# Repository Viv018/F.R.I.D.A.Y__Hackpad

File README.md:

# F.R.I.D.A.Y__Hackpad
This is a Macro pad with a 3x3 key pad along with a rotary encoder and a 0.91 QLED screen for my HACKCLUB project
# F.R.I.D.A.Y

A custom 3×3 macropad with a rotary encoder, 0.91" OLED, and per-key SK6812 RGB lighting, built around the Seeeduino XIAO.

I named it F.R.I.D.A.Y because I wanted something that feels like a helpful little assistant sitting on my desk and cause i am a big marvel fan.

### Features
- 9 mechanical switches (3×3 matrix)
- Rotary encoder with push button
- 0.91" 128×32 OLED display
- 8× SK6812MINI-E reverse-mount RGB LEDs
- Seeed XIAO RP2040
- Fully open source

### Photos

**Schematic**

**PCB**
" src="https://github.com/user-attachments/assets/fc30a773-a280-402c-9867-2068fab1f9ea" />
)

**Case**
 - Autodesk Fusion (Trial ends in 24 days)  8_13_2026 5_06_41 PM.png)

### Bill of Materials

| Part                        | Quantity | Notes                          |
|----------------------------|----------|--------------------------------|
| Seeeduino XIAO             | 1        | RP2040 version                 |
| MX-style switches          | 9        | Any MX compatible              |
| SK6812MINI-E               | 8        | Reverse mount                  |
| 1N4148 diodes              | 9        |                                |
| Rotary Encoder (EC11)      | 1        | With push switch               |
| 0.91" OLED                 | 1        | I2C, 128×32                    |
| Keycaps                    | 9        | 1u                             |
| M3 screws + heat-set inserts | 4      | For the case                   |

### Firmware
This project uses **QMK**

The firmware is located in the `/Firmware` folder.

### Case
The case is a simple two-part sandwich design made in Fusion 360.  
STL/STEP files are available in the `/CAD` and `/production` folders.

### Credits
Designed for Hack Club’s Hackpad program by BATMANNN BABYYY

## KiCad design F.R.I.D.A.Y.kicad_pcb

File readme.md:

# F.R.I.D.A.Y.

This is my custom macropad, F.R.I.D.A.Y. I designed the schematic and PCB
myself in KiCad and wrote the firmware on top of QMK. It's a 3x3 key
matrix (9 keys total, one of them being the rotary encoder's own push
switch), plus the encoder for rotation input, a small OLED screen, and
RGB lighting.

## What's on it

- Seeed XIAO RP2040 as the brains
- 3x3 switch matrix (9 keys), with SW10 (the encoder's push button)
  built into the matrix as one of the 9
- A rotary encoder for scrolling / volume / media control
- A 0.91" OLED (128x32) that shows which layer is active
- 8x SK6812 addressable RGB LEDs

## Pin mapping

I worked this out straight from my schematic:

| Net                | XIAO pin | RP2040 GPIO |
|---------------------|----------|-------------|
| Row 0               | D0       | GP26        |
| Row 1               | D1       | GP27        |
| Row 2               | D2       | GP28        |
| Col 0               | D3       | GP29        |
| SDA (OLED)          | D4       | GP6         |
| SCL (OLED)          | D5       | GP7         |
| PIN7 -> DIN (LEDs)  | D6       | GP0         |
| Col 1               | D7       | GP1         |
| Col 2               | D8       | GP2         |
| ENC_A               | D9       | GP4         |
| ENC_B               | D10      | GP3         |

Key layout, matching the silkscreen on my PCB:

```
[SW10] [SW8] [SW9]     <- SW10 is the encoder's own push button
[SW1]  [SW2] [SW3]
[SW4]  [SW5] [SW6]
```

## Firmware

Built on QMK. There are two layers - a base layer for my everyday keys
and media, and an Fn layer (hold the bottom-right key) for extra
shortcuts. The encoder does volume on the base layer and skips tracks
on the Fn layer. The OLED just shows the current layer for now.

### Building it

```bash
python3 -m pip install qmk
qmk setup
```

Then drop this whole `friday` folder into `~/qmk_firmware/keyboards/friday/`
so it looks like:

```
qmk_firmware/keyboards/friday/
├── keyboard.json
├── config.h
├── rules.mk
├── readme.md
└── keymaps/
    └── default/
        └── keymap.c
```

Compile:

```bash
qmk compile -kb friday -km default
```

That spits out `friday_default.uf2`.

### Flashing

1. Plug the XIAO RP2040 in over USB.
2. Double-tap reset to drop it into UF2 bootloader mode - a drive
   called `RPI-RP2` shows up.
3. Drag `friday_default.uf2` onto that drive. It reboots on its own
   running the new firmware.

## Notes to self

- If a key or the encoder isn't responding, check continuity on that
  net in KiCad first - the pin table above is only as good as the
  actual soldering.
- If the encoder skips two steps per detent (or does nothing), try
  changing `ENCODER_RESOLUTION` in `config.h` between 2 and 4.
- `ENC_C` on the encoder just goes to GND, nothing to configure there.
- RGB is enabled but I haven't bound any keys to control it yet - next
  thing to add.

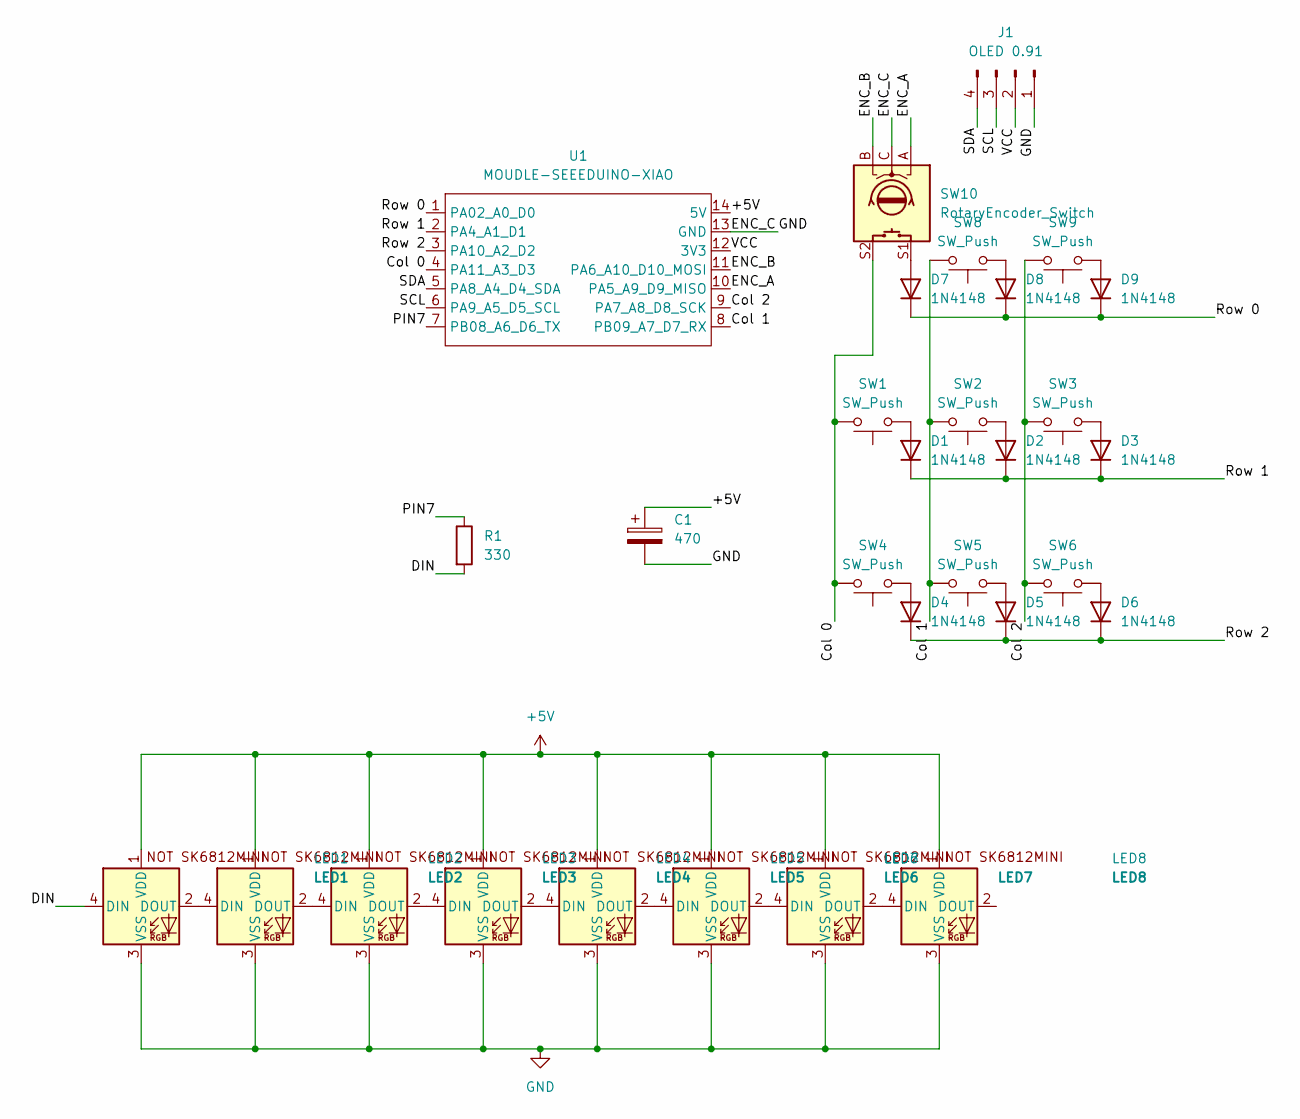
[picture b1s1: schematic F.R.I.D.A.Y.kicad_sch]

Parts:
C1: 470; CP_Axial_L18.0mm_D6.5mm_P25.00mm_Horizontal
D1, D2, D3, D4, D5, D6, D7, D8, D9: 1N4148; D_DO-35_SOD27_P7.62mm_Horizontal
J1: OLED 0.91; ER_OLEDM0.91_1x-I2C
LED1: LED1; LED_SK6812MINI-E_3.2x2.8mm_P1.5mm_ReverseMount
LED2: LED2; LED_SK6812MINI-E_3.2x2.8mm_P1.5mm_ReverseMount
LED3: LED3; LED_SK6812MINI-E_3.2x2.8mm_P1.5mm_ReverseMount
LED4: LED4; LED_SK6812MINI-E_3.2x2.8mm_P1.5mm_ReverseMount
LED5: LED5; LED_SK6812MINI-E_3.2x2.8mm_P1.5mm_ReverseMount
LED6: LED6; LED_SK6812MINI-E_3.2x2.8mm_P1.5mm_ReverseMount
LED7: LED7; LED_SK6812MINI-E_3.2x2.8mm_P1.5mm_ReverseMount
LED8: LED8; LED_SK6812MINI-E_3.2x2.8mm_P1.5mm_ReverseMount
R1: 330; R_Axial_DIN0207_L6.3mm_D2.5mm_P10.16mm_Horizontal
SW1, SW2, SW3, SW4, SW5, SW6, SW8, SW9: SW_Push; SW_Cherry_MX_1.00u_PCB
SW10: RotaryEncoder_Switch; RotaryEncoder_Alps_EC11E-Switch_Vertical_H20mm
U1: MOUDLE-SEEEDUINO-XIAO; XIAO-Generic-Hybrid-14P-2.54-21X17.8MM

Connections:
+5V: C1.1, LED1.1 (VDD), LED2.1 (VDD), LED3.1 (VDD), LED4.1 (VDD), LED5.1 (VDD), LED6.1 (VDD), LED7.1 (VDD), LED8.1 (VDD), U1.14 (5V)
/Col 0: SW1.2, SW4.2, SW10.S2, U1.4 (PA11_A3_D3)
/Col 1: SW2.2, SW5.2, SW8.2, U1.8 (PB09_A7_D7_RX)
/Col 2: SW3.2, SW6.2, SW9.2, U1.9 (PA7_A8_D8_SCK)
/DIN: LED1.4 (DIN), R1.2
/ENC_A: SW10.A, U1.10 (PA5_A9_D9_MISO)
/ENC_B: SW10.B, U1.11 (PA6_A10_D10_MOSI)
/PIN7: R1.1, U1.7 (PB08_A6_D6_TX)
/Row 0: D7.1 (K), D8.1 (K), D9.1 (K), U1.1 (PA02_A0_D0)
/Row 1: D1.1 (K), D2.1 (K), D3.1 (K), U1.2 (PA4_A1_D1)
/Row 2: D4.1 (K), D5.1 (K), D6.1 (K), U1.3 (PA10_A2_D2)
/SCL: J1.3, U1.6 (PA9_A5_D5_SCL)
/SDA: J1.4, U1.5 (PA8_A4_D4_SDA)
/VCC: J1.2, U1.12 (3V3)
GND: C1.2, J1.1, LED1.3 (VSS), LED2.3 (VSS), LED3.3 (VSS), LED4.3 (VSS), LED5.3 (VSS), LED6.3 (VSS), LED7.3 (VSS), LED8.3 (VSS), SW10.C, U1.13 (GND)
unnamed: D1.2 (A), SW1.1
unnamed: D2.2 (A), SW2.1
unnamed: D3.2 (A), SW3.1
unnamed: D4.2 (A), SW4.1
unnamed: D5.2 (A), SW5.1
unnamed: D6.2 (A), SW6.1
unnamed: D7.2 (A), SW10.S1
unnamed: D8.2 (A), SW8.1
unnamed: D9.2 (A), SW9.1
unnamed: LED1.2 (DOUT), LED2.4 (DIN)
unnamed: LED2.2 (DOUT), LED3.4 (DIN)
unnamed: LED3.2 (DOUT), LED4.4 (DIN)
unnamed: LED4.2 (DOUT), LED5.4 (DIN)
unnamed: LED5.2 (DOUT), LED6.4 (DIN)
unnamed: LED6.2 (DOUT), LED7.4 (DIN)
unnamed: LED7.2 (DOUT), LED8.4 (DIN)

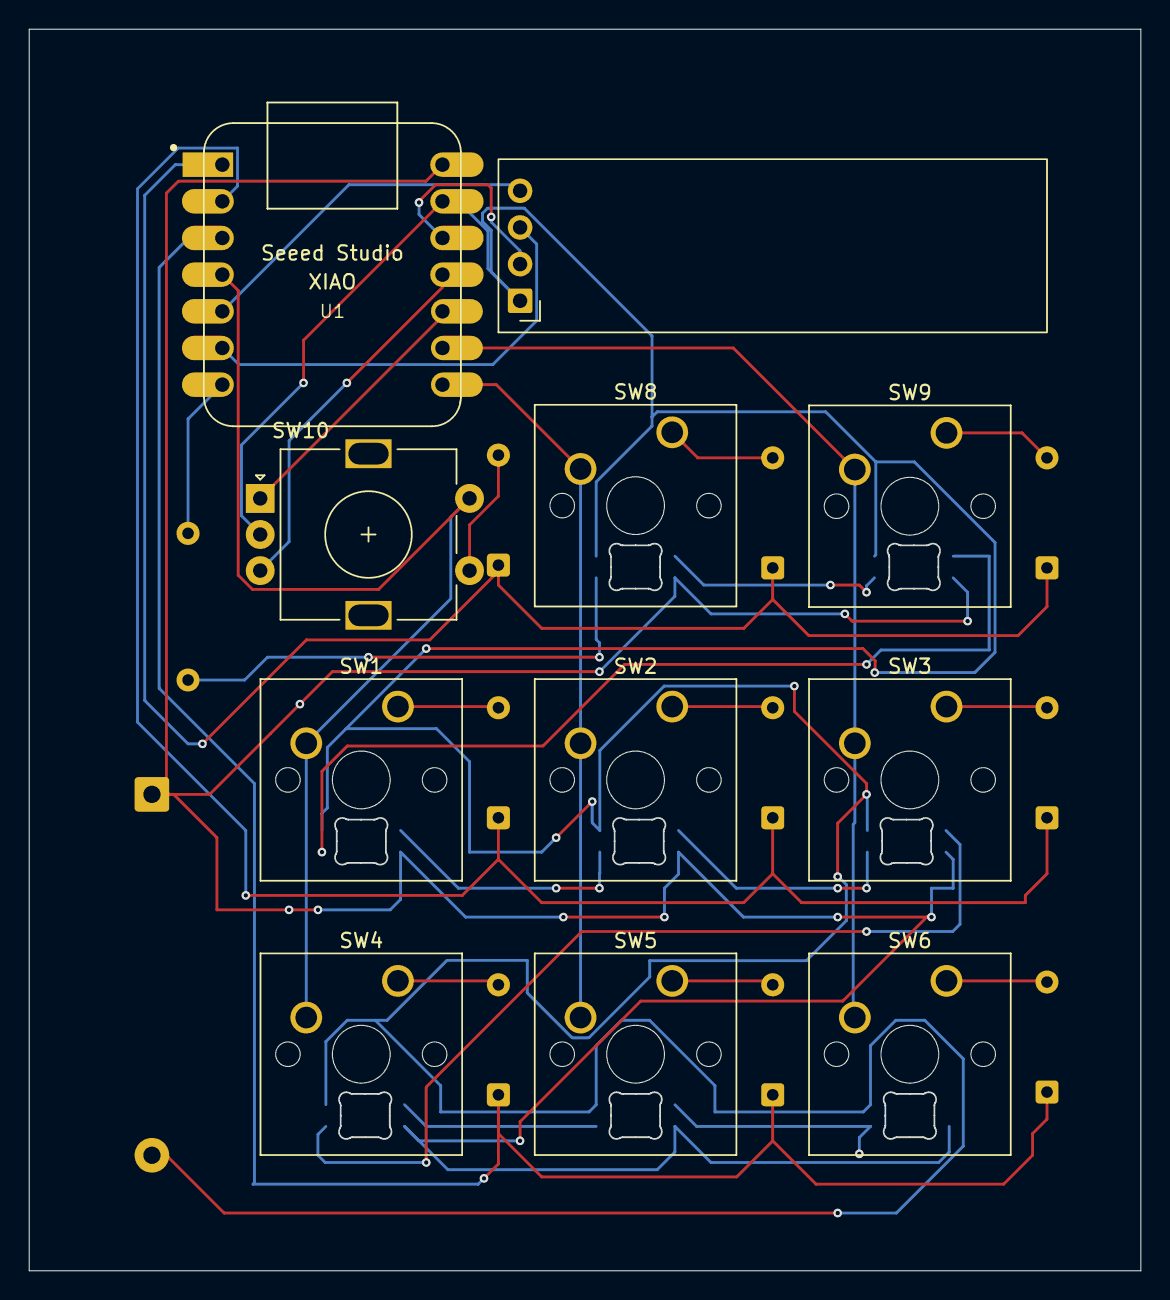
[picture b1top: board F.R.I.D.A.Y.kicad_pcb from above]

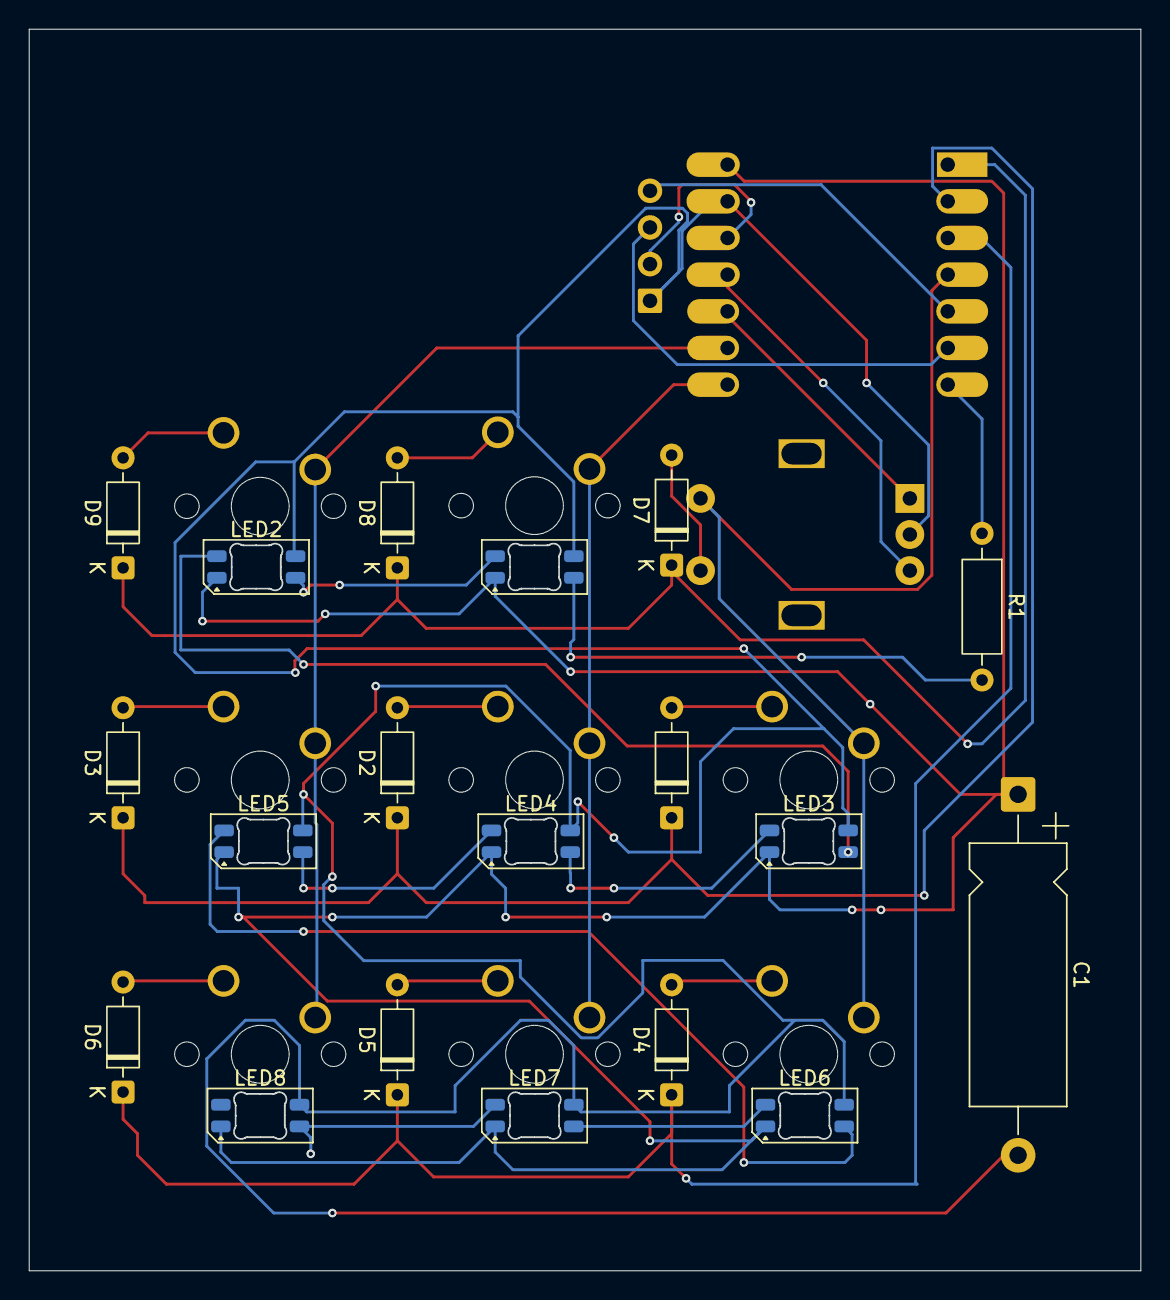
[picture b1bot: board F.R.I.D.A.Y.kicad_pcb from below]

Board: 2 copper layers, 77.0 x 86.0 mm, 30 parts (19 on the bottom side), 31 nets.
